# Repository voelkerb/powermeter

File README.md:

# PowerMeter

The PowerMeter is a WiFi-enabled electricity meter that can also control the connected appliance’s power status.
It enables the recording of high-frequency voltage and current waveforms or integration into smart home systems via protocols such as _MQTT_.
Additional modular components facilitate the integration of other wireless connectivity options, including LoRaWAN, and the embedding of additional sensors within the housing. 

### Clone this repo with
```bash
git clone --recurse-submodules git@github.com:voelkerb/powermeter.git
```

If you are interested in gathering the entire house energy consumption, please refer to the [SmartMeter](https://github.com/voelkerb/smartmeter) instead.

## Hardware Version _1_ vs _2_
The development commenced with hardware [version 1.0](Schematic/Version_1). It comprises an ESP8266 microcontroller and a dedicated electricity monitoring chip. As the primary objective of this project was to record voltage and current waveforms at elevated frequencies, several limitations associated with this application were addressed in hardware [version 2.0](Schematic/Version_2). This version features a more powerful microcontroller with 8MB of internal storage for data buffering, an RTC for precise sampling and timekeeping, and a full 16A relay, enabling the control of high-power appliances such as dishwashers. The USB connection present in hardware [version 1.0](Schematic/Version_1) has been eliminated, but could be reintroduced with an additional extension board.

## Why to use?
It's open source, easy to use, easy to build and offers lots of flexibility. 

The hardware is...
* tested to work reliable with 230V.
* flexible enough to be integrated into existing projects.
* extendable via a UART interface.
* rather cheap (all components sum up to around 30€).

The firmware supports...
* existing 2.4GHz WPA2 networks or can create its own network.
* to receive commands via USB, TCP or MQTT.
* to store the configuration in the internal non volatile memory.
* to provide data at sampling rates from 1/5Hz all the way up to 8kHz.
* to calibrate the measurements.
* integration into most existing smart home systems e.g. HomeKit (via homebridge and MQTT).
* FFMpeg streaming. This allows to store high frequency data directly into files (e.g. MKV).

## How to build one?
Are you interested in constructing your own PowerMeter? Since the PCBs are provided in this repository, you can simply assemble your own.

Depending on your specific requirements, you may choose to build either [Version 1.0](/Schematic/Version_1) or [Version 2.0](/Schematic/Version_2).
* [Version 1.0](/Schematic/Version_1) incorporates an ESP8266 microcontroller and a 10A solid-state relay.
    * Advantages:
        * The components are more cost-effective (approximately 30€).
        * It includes a USB interface for uploading the firmware or streaming data.
    * Disadvantages:
        * It lacks modularity.
        * The 10A relay can only switch connected appliances with a maximum power consumption of less than 2300 Watt.
* [Version 2.0](/Schematic/Version_2) features an ESP32 microcontroller and a 16A bistable relay.
    * Advantages:
        * You can switch appliances with a maximum power consumption of up to 3600 Watt.
        * It possesses a multi-core microcontroller that also supports Bluetooth.
        * 8MB of internal storage enables data buffering. If you stream high-frequency data at, for instance, 2kHz, this can accommodate up to 500s of data during network interruptions.
        * An RTC maintains timekeeping, allowing you to synchronize sampling rates during high-frequency sampling.
        * It can be extended by stacking additional modules on an extension header.
    * Disadvantages:
        * The cost of the components is slightly higher (approximately 35€).

Steps to build your own PowerMeter:

1. Create the PCB ([version 1.0](/Schematic/Version_1)) or [version 2.0](/Schematic/Version_2))). We recommend using [JLC PCB](https://jlcpcb.com) because it’s very affordable and the quality is still good.
2. Purchase the components listed in the [BOM](/BOM) (Bill of Materials).
3. Solder everything together. We used a small reflow oven, but a fine soldering iron could also be used.
4. Buy a matching housing. We highly recommend using [this one](https://www.conrad.de/de/p/bopla-eletec-se-432-de-cee-stecker-gehaeuse-120-x-65-x-50-abs-polycarbonat-lichtgrau-graphitgrau-1-st-522228.html) because the PCB was specially designed for it, the mounting holes match, and it’s safe to use with 230V. We also tried custom 3D prints (see [CAD](/CAD)), but it’s at your own risk.

5. Wire the PowerMeters using the provided diagram. 

6. Upload the [firmware](/Firmware) according to the instructions for your version. 
7. Interface with the PowerMeter according to the protocol documented [here](/docu/README_Firmware_Cmds.md) 

# Use cases
## Smart homes
There are plenty of use cases for a smart plug inside a smart home.
* Switch appliances _on_ and _off_ using a voice assistant or your smartphone
* Include it in home automation software to switch appliances based on automations, e.g.: 
    * Switch appliances _on_ and _off_ by time of day.
    * Switch appliances _off_ automatically at standby consumption.
    * Trigger an alert if the consumption exceeds a limit.

* Monitor the power consumption of an appliance over day. See this faulty fridge as an example.

## For research purpose
* Analyze high frequency voltage and current waveforms.

* Record high frequency electricity datasets (see e.g. the [FIRED](https://github.com/voelkerb/FIRED_dataset_helper) dataset which can be used for Non-Intrusive Load Monitoring).

# License:
## Firmware:
Copyright (c) 2019 Benjamin Völker. All rights reserved.
This work is licensed under the terms of the [CC 4.0 licence](https://creativecommons.org/licenses/by/4.0/).

## Hardware:
Copyright (c) 2019 Benjamin Völker. All rights reserved.
This work is licensed under the terms of the [TAPR Open Hardware License](https://web.tapr.org/TAPR_Open_Hardware_License_v1.0.txt).

# Reference

Please cite our publications if you compare to or use this system:
* Benjamin Völker, Philipp M. Scholl, and Bernd Becker. 2019. Semi-Automatic Generation and Labeling of Training Data for Non-intrusive Load Monitoring. In Proceedings of the Tenth ACM International Conference on Future Energy Systems (e-Energy '19). Association for Computing Machinery, New York, NY, USA, 17–23. DOI:https://doi.org/10.1145/3307772.3328295
 
* Benjamin Völker, Marc Pfeifer, Philipp M. Scholl, and Bernd Becker. 2020. FIRED: A Fully-labeled hIgh-fRequency Electricity Disaggregation Dataset. In Proceedings of the 7th ACM International Conference on Systems for Energy-Efficient Buildings, Cities, and Transportation (BuildSys '20). Association for Computing Machinery, New York, NY, USA, 294–297. DOI:https://doi.org/10.1145/3408308.3427623

* Völker, B.; Pfeifer, M.; Scholl, P.M.; Becker, B. A Framework to Generate and Label Datasets for Non-Intrusive Load Monitoring. Energies 2021, 14, 75. https://doi.org/10.3390/en14010075

Kudos also go to Pascal Verboket & Valentin Czisch for developing the first draft schematics prior to [Version 1.0](/Schematic/Version_1).

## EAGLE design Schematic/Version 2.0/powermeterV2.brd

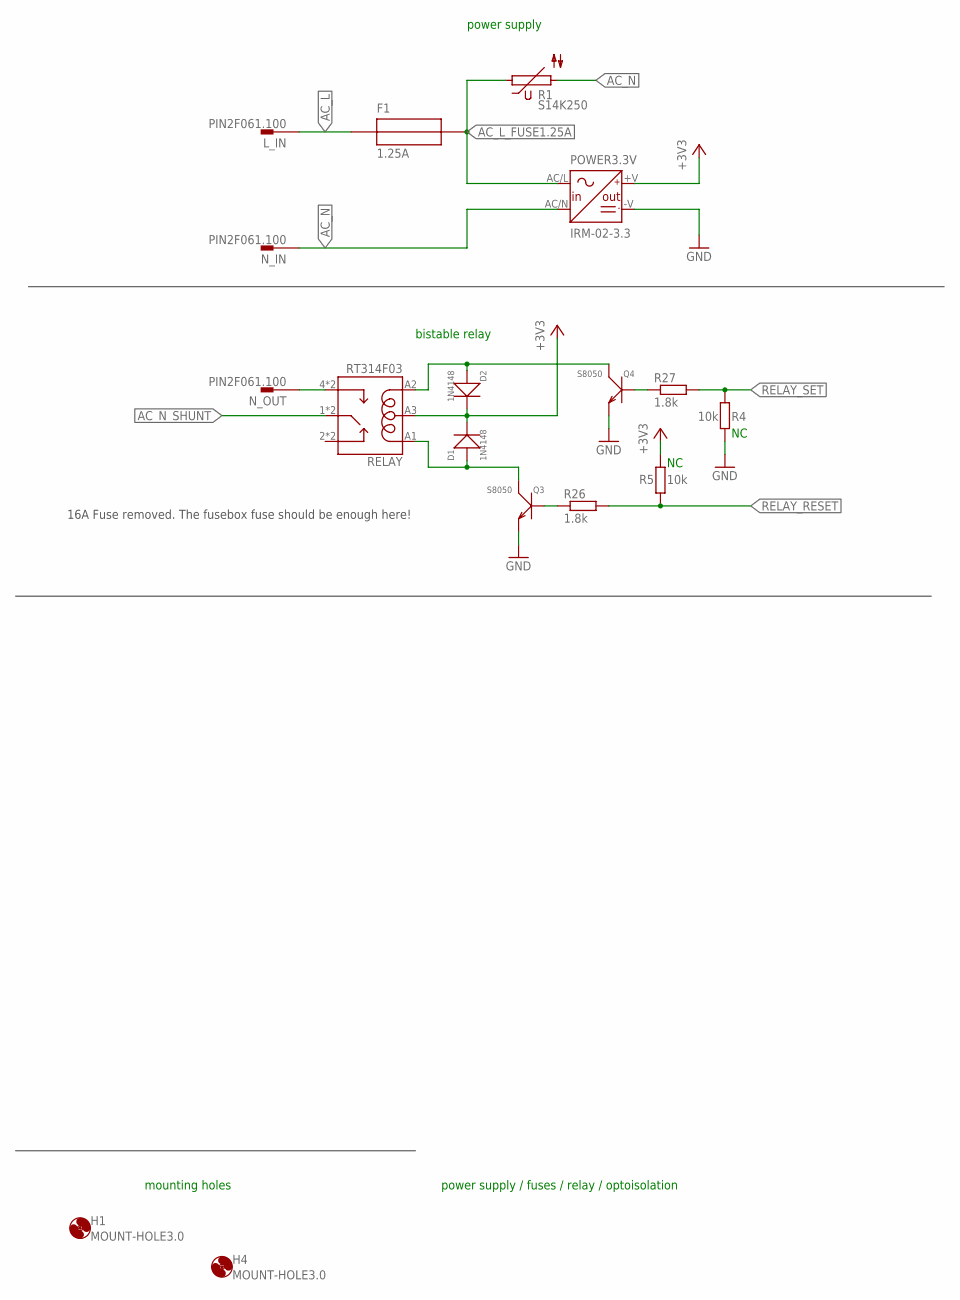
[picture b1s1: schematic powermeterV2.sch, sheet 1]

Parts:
D1, D2: 1N4148; LL-34
F1: 1.25A; SMD_FUSE
H1, H4: MOUNT-HOLE3.0; 3,0
L_IN: PIN2F061.100; F061.100
N_IN: PIN2F061.100; F061.100
N_OUT: PIN2F061.100; F061.100
POWER3.3V: IRM-02-3.3; MW_IRM-02
Q3, Q4: S8050; SOT-23
R1: S14K250
R4, R5: 10k; R0402
R26, R27: 1.8k; R0402
RELAY: RT314F03; RELAY_RT314F03

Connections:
+3V3: D1.C (-), D2.C (-), POWER3.3V.+V (+V_OUT), R5.2, RELAY.A3; also elsewhere on the board
AC_L: F1.P$1 (1), L_IN.A1, L_IN.A2; also elsewhere on the board
AC_L_FUSE1.25A: F1.P$2 (2), POWER3.3V.AC/L (L), R1.1
AC_N: N_IN.A1, N_IN.A2, POWER3.3V.AC/N (N), R1.2; also elsewhere on the board
AC_N_SHUNT: RELAY.1 (11), RELAY.11; also elsewhere on the board
GND: POWER3.3V.-V (-V_OUT), Q3.2 (E), Q4.2 (E), R4.2; also elsewhere on the board
unnamed: N_OUT.A1, N_OUT.A2, RELAY.4 (14), RELAY.14
unnamed: Q3.1 (B), R26.1
unnamed: D1.A (+), Q3.3 (C), RELAY.A1
unnamed: Q4.1 (B), R27.1
unnamed: D2.A (+), Q4.3 (C), RELAY.A2
RELAY_RESET: R5.1, R26.2; also elsewhere on the board
RELAY_SET: R4.1, R27.2; also elsewhere on the board

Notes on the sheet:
power supply / fuses / relay / optoisolation
power supply
bistable relay
mounting holes
16A Fuse removed. The fusebox fuse should be enough here!

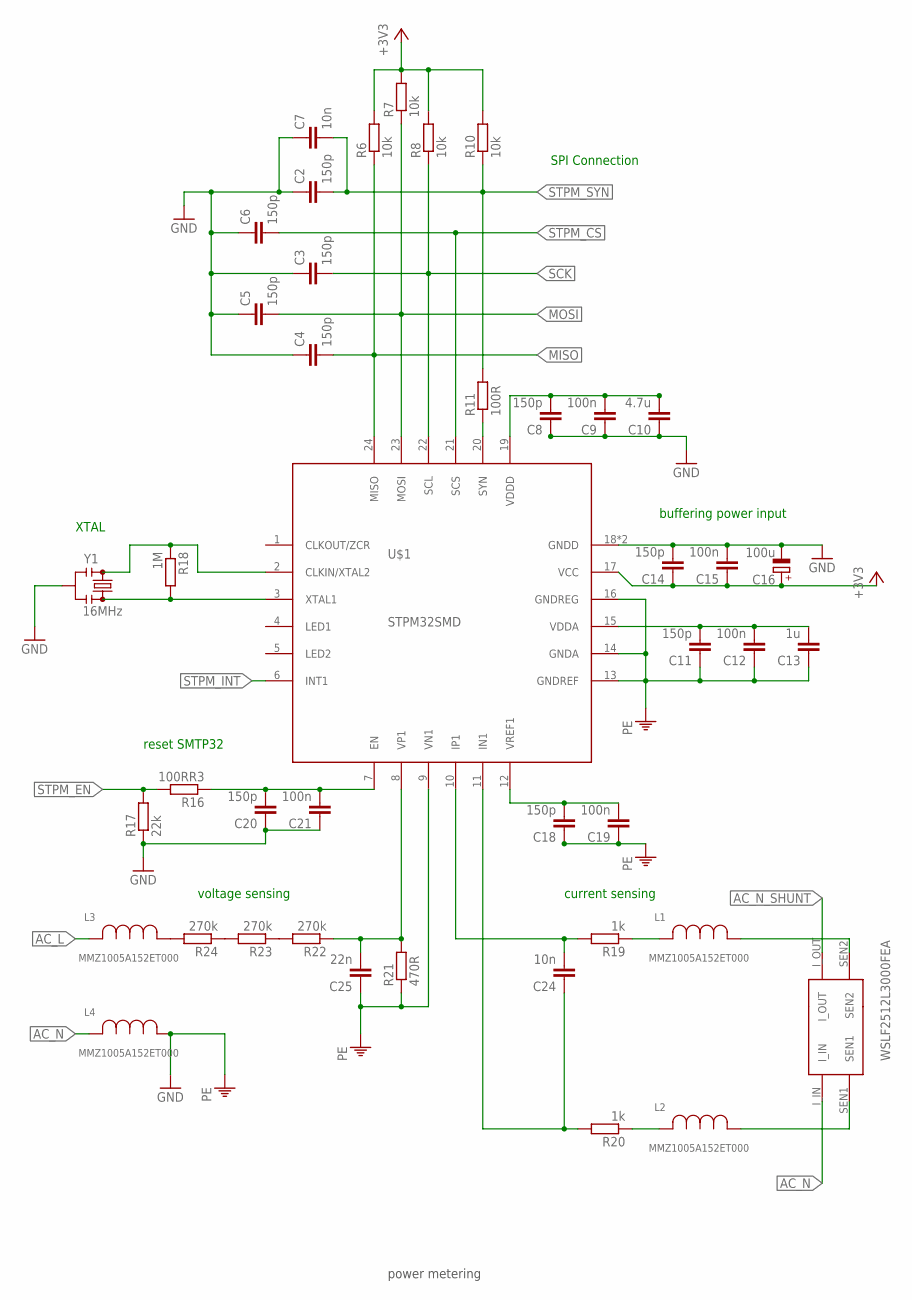
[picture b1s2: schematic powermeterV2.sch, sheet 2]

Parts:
C2, C3, C4, C5, C6, C8, C11, C14, C18, C20: 150p; C0402
C7, C24: 10n; C0603
C9, C12, C15, C19, C21: 100n; C0603
C10: 4.7u; C0805
C13: 1u; C0603
C16: 100u; D/7343-31W
C25: 22n; C0603
L1, L2, L3, L4: MMZ1005A152ET000; IND_1005
R6, R7, R8, R10: 10k; R0603
R11: 100R; R0603
R16: 100RR3; R0603
R17: 22k; R0603
R18: 1M; R0603
R19, R20: 1k; R0603
R21: 470R; M1206
R22, R23, R24: 270k; M1206
SHUNT: WSLF2512L3000FEA; SMD_SHUNT
U$1: STPM32SMD; QFN24
Y1: 16MHz; RESONATOR-SMD-3.2X1.3

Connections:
+3V3: C14.1, C15.1, C16.+, R6.2, R7.2, R8.2, R10.2, U$1.17 (VCC); also elsewhere on the board
AC_L: L3.2; also elsewhere on the board
AC_N: L4.2, SHUNT.I_IN; also elsewhere on the board
AC_N_SHUNT: SHUNT.I_OUT; also elsewhere on the board
DC_GND1: C18.2, C19.2, U$1.12 (VREF1)
DC_GND2: C20.2, C21.2, R16.1, U$1.7 (EN)
GND: C2.1, C3.1, C4.1, C5.1, C6.1, C7.1, C8.1, C9.1, C10.1, C11.1, C12.1, C13.1, C14.2, C15.2, C16.-, C18.1, C19.1, C20.1, C21.1, C25.1, L4.1, R17.1, R21.1, U$1.9 (VN1), U$1.13 (GNDREF), U$1.14 (GNDA), U$1.16 (GNDREG), U$1.18 (GNDD), U$1.EXP (GNDD), Y1.2; also elsewhere on the board
MISO: C4.2, R6.1, U$1.24 (MISO); also elsewhere on the board
MOSI: C5.2, R7.1, U$1.23 (MOSI); also elsewhere on the board
unnamed: C8.2, C9.2, C10.2, U$1.19 (VDDD)
unnamed: C11.2, C12.2, C13.2, U$1.15 (VDDA)
unnamed: R18.2, U$1.3 (XTAL1), Y1.3
unnamed: R18.1, U$1.2 (CLKIN/XTAL2), Y1.1
unnamed: C24.1, R20.2, U$1.11 (IN1)
unnamed: R11.1, U$1.20 (SYN)
unnamed: C24.2, R19.2, U$1.10 (IP1)
unnamed: C25.2, R21.2, R22.1, U$1.8 (VP1)
unnamed: R23.2, R24.1
unnamed: R22.2, R23.1
unnamed: L3.1, R24.2
unnamed: L1.2, R19.1
unnamed: L2.2, R20.1
unnamed: L1.1, SHUNT.SEN2
unnamed: L2.1, SHUNT.SEN1
SCK: C3.2, R8.1, U$1.22 (SCL); also elsewhere on the board
STPM_CS: C6.2, U$1.21 (SCS); also elsewhere on the board
STPM_EN: R16.2, R17.2; also elsewhere on the board
STPM_INT: U$1.6 (INT1)
STPM_SYN: C2.2, C7.2, R10.1, R11.2; also elsewhere on the board

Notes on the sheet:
power metering
SPI Connection
buffering power input
reset SMTP32
XTAL
current sensing
voltage sensing

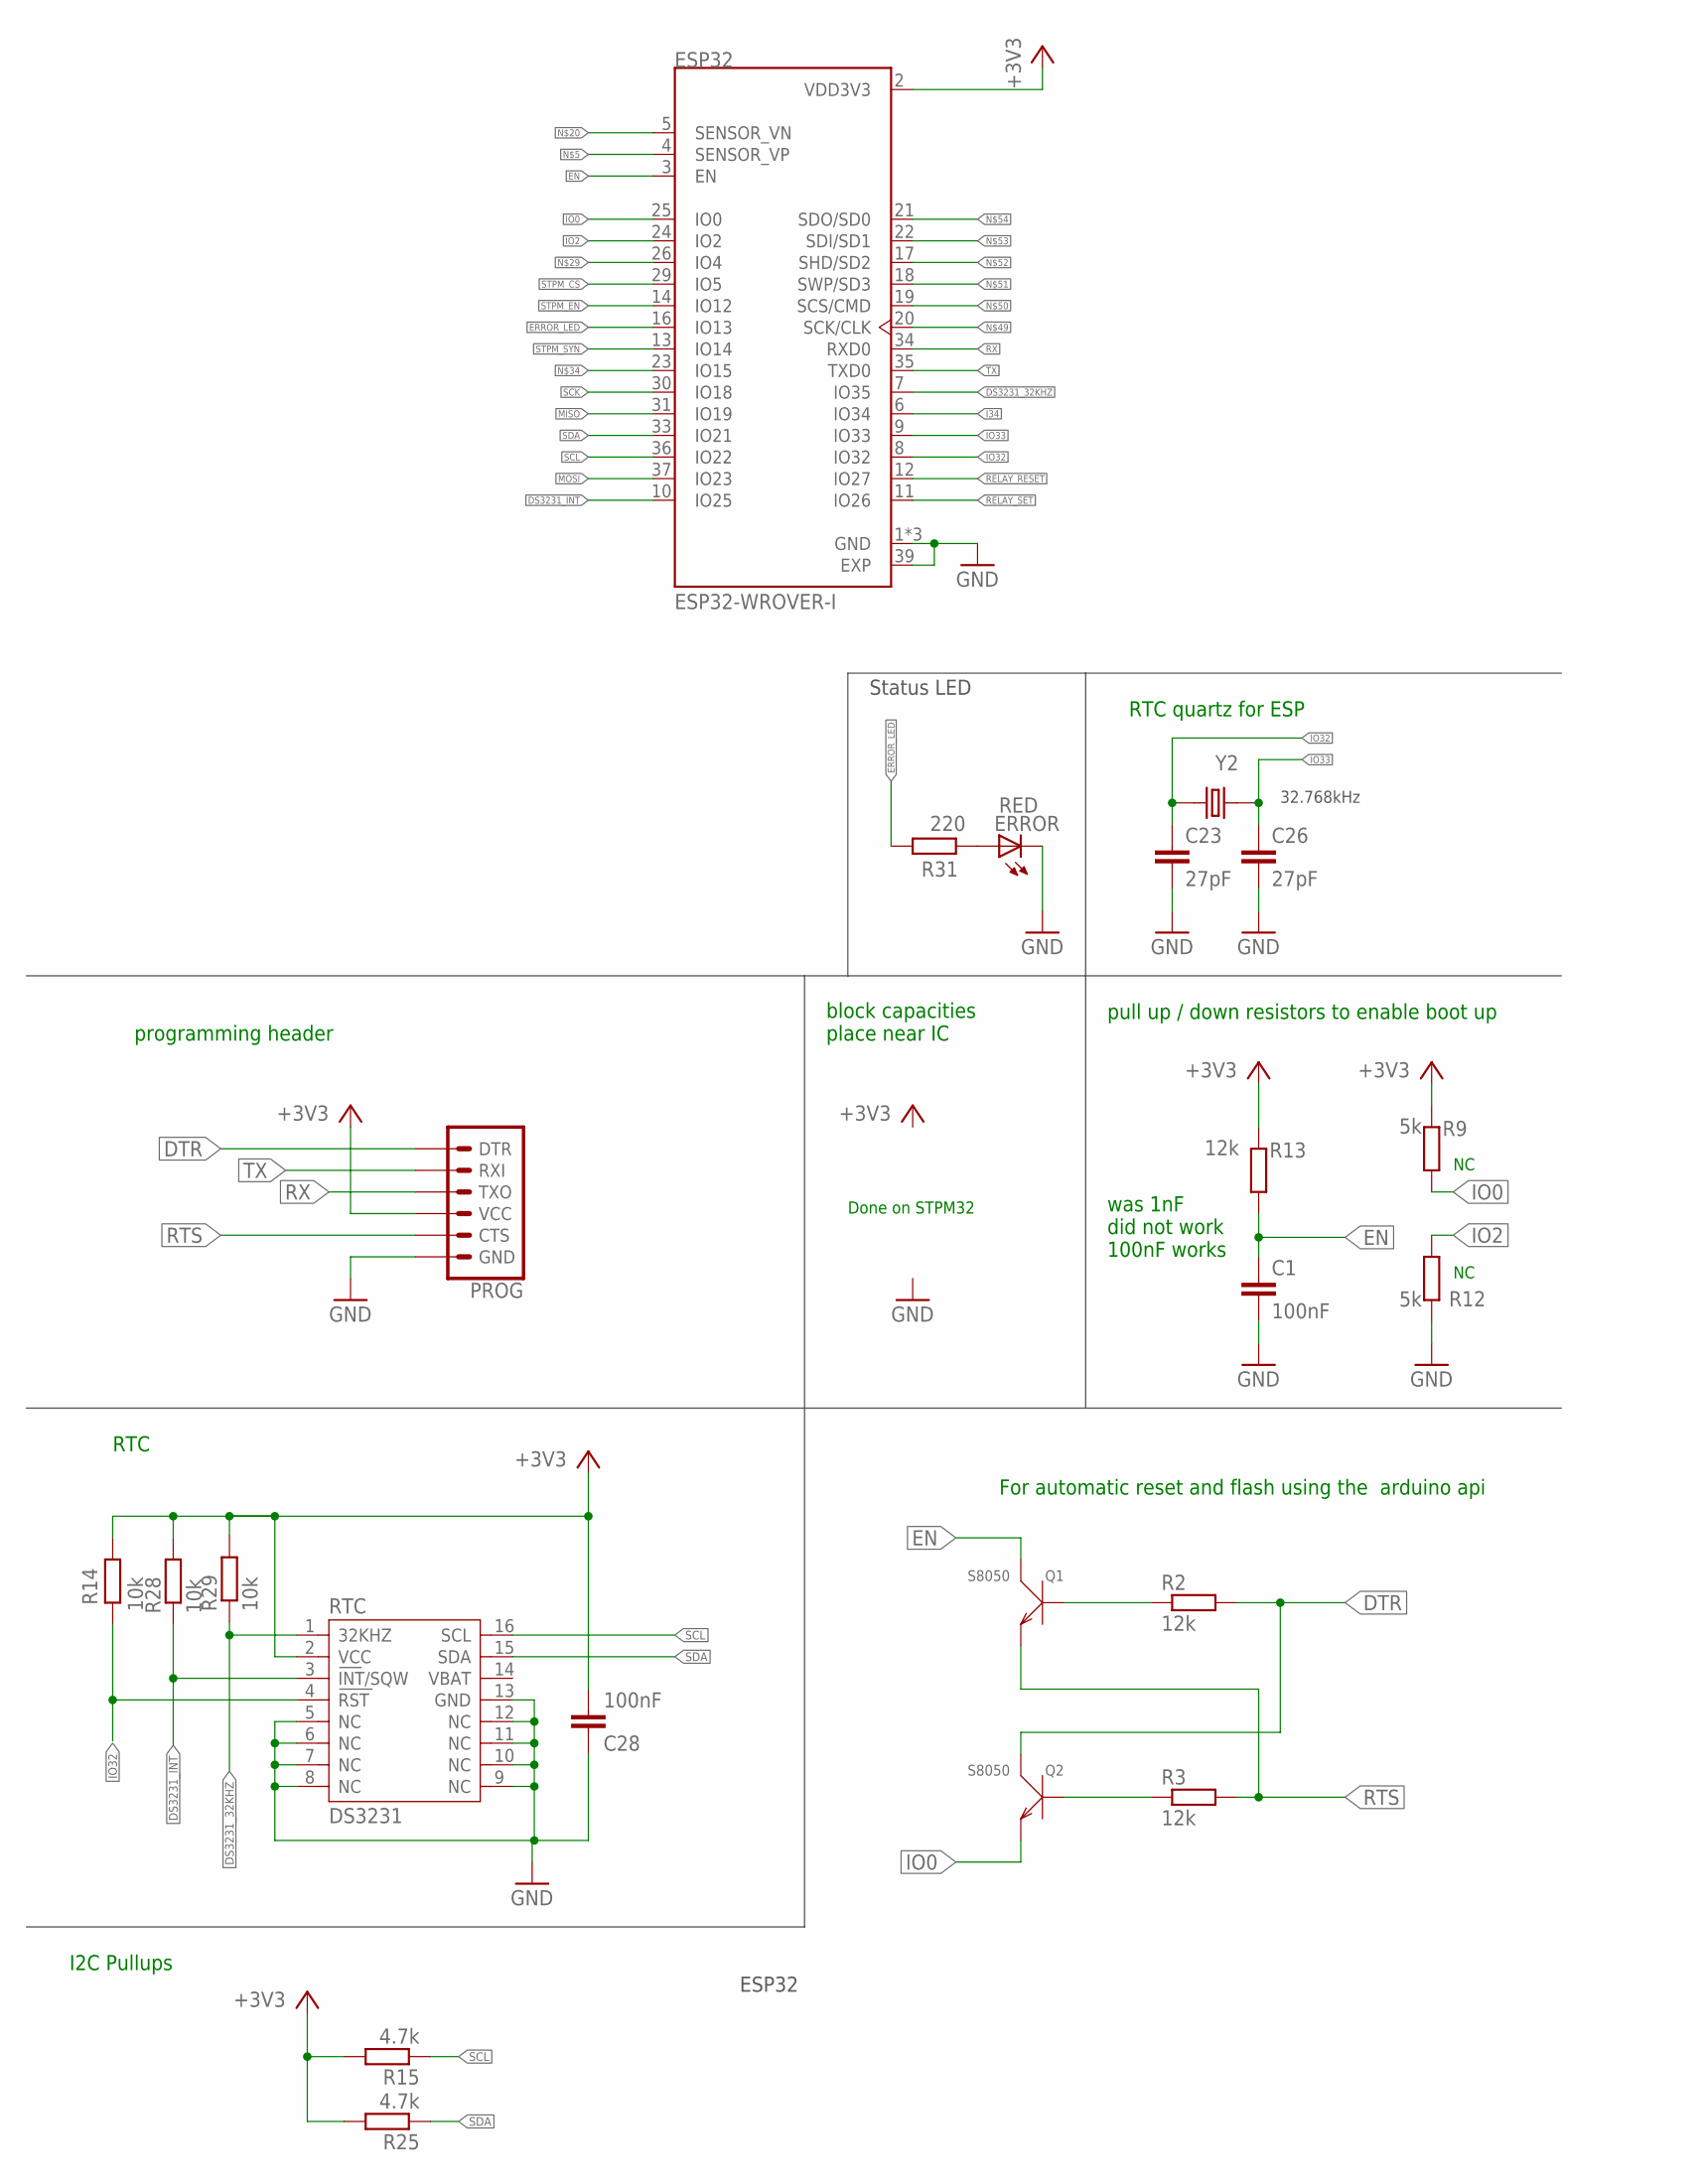
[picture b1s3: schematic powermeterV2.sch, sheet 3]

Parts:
C1, C28: 100nF; C0402
C23, C26: 27pF; C0402
ERROR: RED; CHIP-LED0805
ESP32: ESP32-WROVER-I; XCVR_ESP32-WROVER-I
PROG: 6_PIN_SERIAL_TARGET; 1X06
Q1, Q2: S8050; SOT-23
R2, R3, R13: 12k; R0402
R9, R12: 5k; R0402
R14, R28, R29: 10k; R0603
R15, R25: 4.7k; R0603
R31: 220; R0603
RTC: DS3231
Y2: NX2012SA-32.768K-STD-MUB-1; XTAL_NX2012SA-32.768K-STD-MUB-1

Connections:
+3V3: C28.2, ESP32.2 (VDD3V3), PROG.4 (VCC), R9.1, R13.1, R14.1, R15.2, R25.2, R28.2, R29.2, RTC.2 (VCC); also elsewhere on the board
DS3231_32KHZ: ESP32.7 (IO35), R29.1, RTC.1 (32KHZ)
DS3231_INT: ESP32.10 (IO25), R28.1, RTC.3 (INT/SQW)
DTR: PROG.1 (DTR), Q2.3 (C), R2.2
EN: C1.1, ESP32.3 (EN), Q1.3 (C), R13.2
ERROR_LED: ESP32.16 (IO13), R31.1
GND: C1.2, C23.2, C26.2, C28.1, ERROR.C, ESP32.1 (GND), ESP32.15 (GND), ESP32.38 (GND), ESP32.39 (EXP), PROG.6 (GND), R12.1, RTC.5 (NC), RTC.6 (NC), RTC.7 (NC), RTC.8 (NC), RTC.9 (NC), RTC.10 (NC), RTC.11 (NC), RTC.12 (NC), RTC.13 (GND); also elsewhere on the board
I34: ESP32.6 (IO34)
IO0: ESP32.25 (IO0), Q2.2 (E), R9.2
IO2: ESP32.24 (IO2), R12.2
IO32: C23.1, ESP32.8 (IO32), R14.2, RTC.4 (RST), Y2.1
IO33: C26.1, ESP32.9 (IO33), Y2.2
MISO: ESP32.31 (IO19); also elsewhere on the board
MOSI: ESP32.37 (IO23); also elsewhere on the board
unnamed: Q1.1 (B), R2.1
unnamed: Q2.1 (B), R3.1
unnamed: ERROR.A, R31.2
RELAY_RESET: ESP32.12 (IO27); also elsewhere on the board
RELAY_SET: ESP32.11 (IO26); also elsewhere on the board
RTS: PROG.5 (CTS), Q1.2 (E), R3.2
RX: ESP32.34 (RXD0), PROG.3 (TXO)
SCK: ESP32.30 (IO18); also elsewhere on the board
SCL: ESP32.36 (IO22), R15.1, RTC.16 (SCL)
SDA: ESP32.33 (IO21), R25.1, RTC.15 (SDA)
STPM_CS: ESP32.29 (IO5); also elsewhere on the board
STPM_EN: ESP32.14 (IO12); also elsewhere on the board
STPM_SYN: ESP32.13 (IO14); also elsewhere on the board
TX: ESP32.35 (TXD0), PROG.2 (RXI)

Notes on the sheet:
pull up / down resistors to enable boot up
For automatic reset and flash using the arduino api
ESP32
block capacities place near IC
Done on STPM32
32.768kHz
RTC quartz for ESP
RTC
programming header
I2C Pullups
Status LED
was 1nF did not work 100nF works

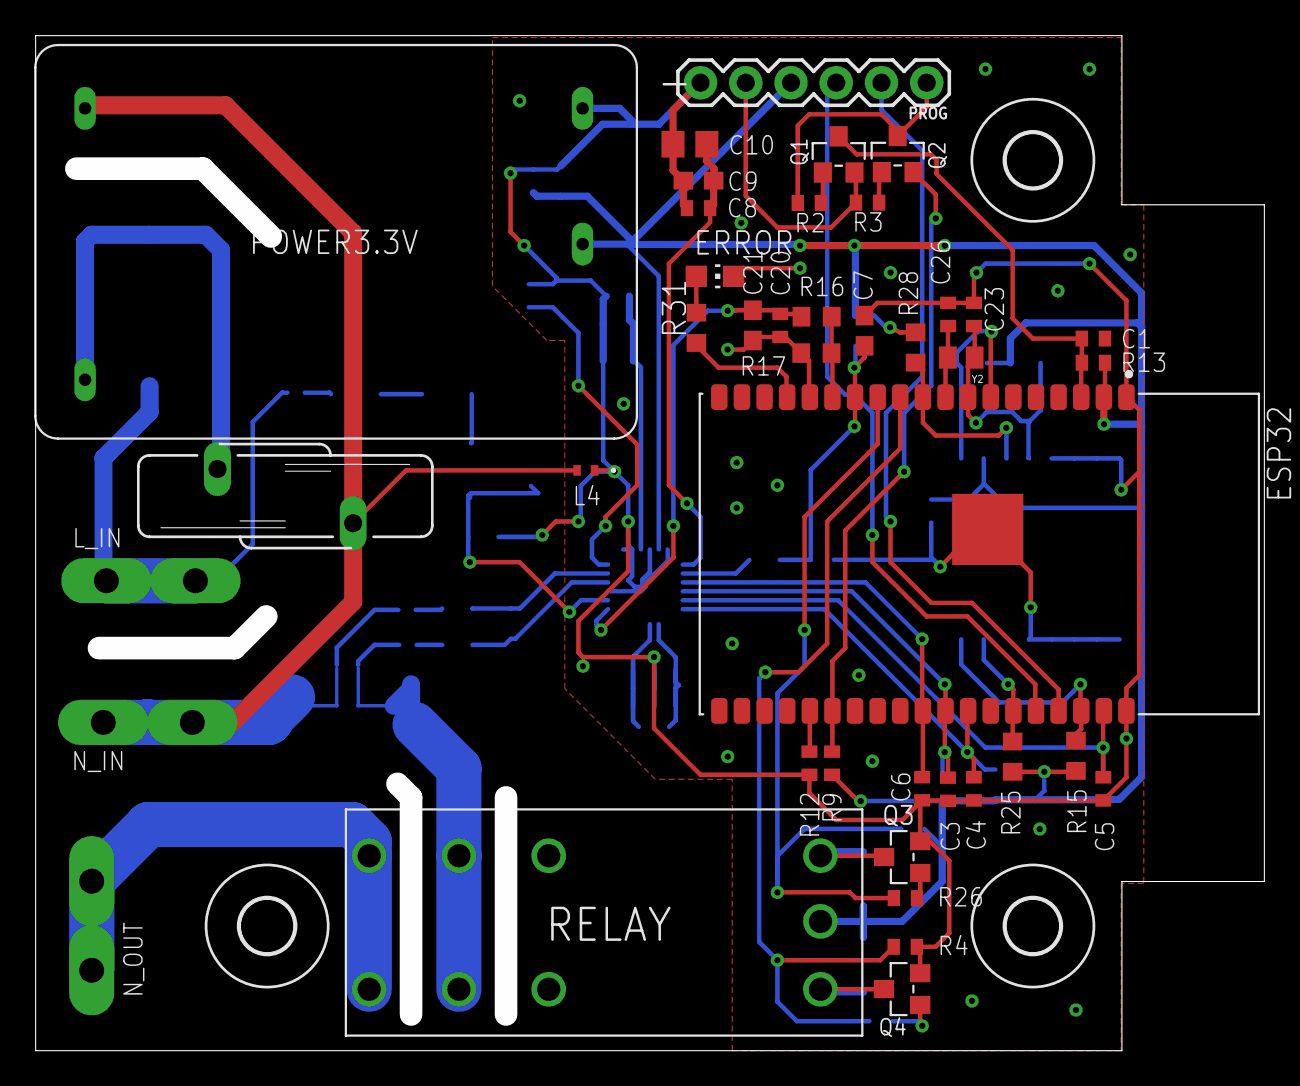
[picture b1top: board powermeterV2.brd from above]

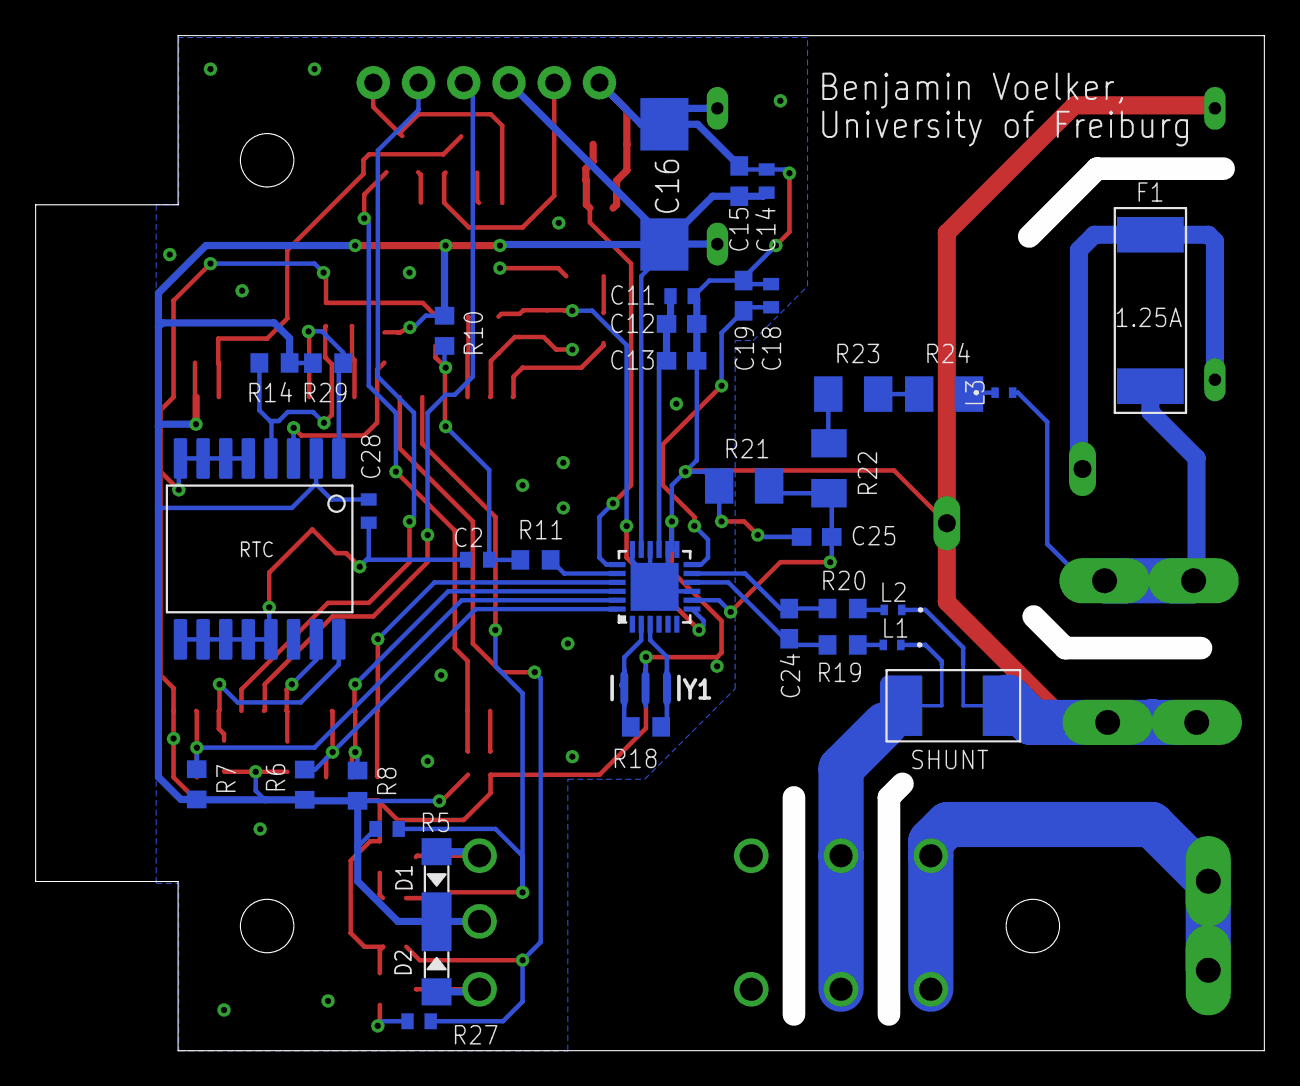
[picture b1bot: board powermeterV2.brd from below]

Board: 2 copper layers, 67.7 x 55.7 mm, 82 parts (38 on the bottom side), 53 nets.

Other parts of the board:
H2: MOUNT-HOLE3.0; 3,0

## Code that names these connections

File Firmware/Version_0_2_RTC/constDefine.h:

// Serial Speed and DEBUG option
#define SERIAL_SPEED 2000000
// #define DEBUG_DEEP
#define SENT_LIFENESS_TO_CLIENTS


#define VERSION "0.2_x_rtc"

// Default values
#define STANDARD_UDP_PORT 54323
#define STANDARD_TCP_SAMPLE_PORT 54321
#define STANDARD_TCP_STREAM_PORT 54322
#define DEFAULT_SR 4000


// Location time difference between us (Freiburg, Germany) and NTP time 
#define LOCATION_TIME_OFFSET 7200 // 2 hours or (2*60*60)


const char * LOG_FILE = "/log.txt";

const char* ntpServerName = "time.uni-freiburg.de";//"0.de.pool.ntp.org";

const char LOG_PREFIX_SERIAL[] = "";
const char LOG_PREFIX[] = "Info:";

// Pin definitions
// Red error led for first flash
const int ERROR_LED = 13;

// Pins for STPM34 SPI Connection
const int STPM_CS = 5;
const int STPM_SYN = 14;
// Reset pin of STPM
const int STPM_RES = 12;

// Pins for 230V Relay
const int RELAY_PIN_S = 26;
const int RELAY_PIN_R = 27;

// Pins for RTC conenction
const int RTC_INT = 25;
const int RTC_32k = 35;
const int RTC_RST = 32;


// Buffering stuff
#define MAX_SEND_SIZE 512 // 1024
// PSRAM Buffer
const int PS_BUF_SIZE = 3*1024*1024 + 512*1024;
#define COMMAND_MAX_SIZE 400

// Communication commands
#define CMD_SAMPLE "sample"
#define CMD_SWITCH "switch"
#define CMD_STOP "stop"
#define CMD_RESTART "restart"
#define CMD_RESET "factoryReset"
#define CMD_INFO "info"
#define CMD_MDNS "mdns"
#define CMD_NTP "ntp"
#define CMD_ADD_WIFI "addWifi"
#define CMD_REMOVE_WIFI "delWifi"
#define CMD_CLEAR_LOG "clearLog"
#define CMD_GET_LOG "getLog"

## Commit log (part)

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2018-11-07 Initial commit of latest files
2018-11-07 added library for stpm32
2018-11-07 deleted
2018-11-12 Fixed regular streaming
2018-11-23 added current version
2018-12-06 Fixed that NTP timed recordings can also be startet using tcp clients
2018-12-19 Disabled Autolatching in favour of manual latching to prevent data glitches! Added CRC disable option and autolatch On option. Tested until 8kHz even if the stpm only supports 7.8125kHz.
2018-12-19 Master Merge
2018-12-20 MDNS name is now read from EEPROM, EEPROM has to be written to at least once s.t. this works
2019-01-07 added ability to set mdns name using serial or tcp command -> Command: 'n12' sets mdns name to powermeter12
2019-03-06 Changed nbuffering to a ringbuffer, version 0.1 kept. Exceptions might still occur. Mutual exclusion problem?
2019-08-05 added version 0_2_x TODO: We need SPIFFS integration to prevent data loss
2019-09-06 Ported to ESP32
2019-09-18 Firmware is now object oriented with RTC support
2019-09-27 new firmware with RTC support, PSRAM, new schematic/board with error LED, I2C pullups etc, diodes
2019-10-16 objectify + added logger, timehandler
2019-11-06 added release ota folder
2019-11-08 added new version where SPI is not in interrupt
2019-11-11 added ethernet support
2019-11-11 added submodules
2019-11-11 removed untracked submodules
2019-11-12 Removed submodule temporarly
2019-11-12 cleaned submodules
2019-11-25 added Version 1 as last version for old HW revision 1.0
2019-12-13 cleanup
2019-12-13 renamed
2019-12-13 cleanup after renaming
2020-01-20 Version renumbering. Hardware Version 1 will now work with Software Version and Hardware Version 2 requires Software Version >= 2
2020-01-21 added multiclient support for tcp
2020-01-22 minor bugfixes
2020-01-22 fixed board/schematic inconsistencies. added 100nF on IO0
2020-02-04 fixed versioning
2020-02-05 added MQTT
2020-02-06 added parsing ino file, added mqtt state request
2020-02-18 rewrite to mqtt class closing ticket 445
2020-02-18 added sampleCB function, network switch is now not possible while sampling or OTA
2020-02-19 added mqtt sampling, closing ticket #442
2020-02-19 added streamserver functionality closing feature #438
2020-02-19 hotfix of OTA not working due to streamserver connect
2020-02-20 fixed issue #453 -> null on mqtt sampling and #454 -> stop command
2020-03-09 added time server command
2020-03-09 minor bugfix
2020-03-12 Closing #459 parallel ntp sync
2020-03-13 added alldevicesettingsgetter blank file
2020-03-13 added network submodule
2020-03-13 Removed submodule
2020-03-17 Added MQTT for homebridge to close #46
2020-03-19 fixed #462 and #463
2020-04-23 added flow control, fixing #469, #470, #471, #474, used snprintf
2020-04-28 saving work for #481 #477
2020-05-13 last stable version
2020-05-18 more priority for sampling task, hopefully fixing #487
2020-05-18 minor improvements
2020-05-18 added ntp correction only for certain confidence level
2021-02-24 Speed up MQTT Reconnect and support mqtt retained switches
2021-02-24 updates submodules
2021-03-01 save
2021-03-01 resstructure
2021-03-01 submodules
2021-03-01 stash
2021-03-01 submoduels reinitialized
2021-03-01 fixed network branch
2021-03-02 added docu
2021-03-02 more docu
2021-03-02 removed zips
2021-03-02 renamed schematic folder
2021-03-02 added why to use
2021-03-02 unify version 2 and version 1 command code
2021-03-03 changed software timers to use unsigned int
2021-03-03 chenged timer to unsigned int
2021-03-03 added update poll function for networjk
2021-03-03 changed Buff size
2021-03-03 gitmodules
2021-03-18 Fixed MQTT msg too often
2021-08-03 added lorawan class
2021-08-03 added support for LoRaWAN
2021-08-03 added support for private key file
2021-08-03 no use lora class to construct message from bytes
2021-08-03 config does now use standard WIFI PWDs from external file
2021-08-03 constDefined includes private file with keys
2021-08-03 Lora support added
2021-08-03 added
2021-08-03 added preprocessor settings docu
2021-08-03 added Lorawan commands
2021-08-03 fixed lorawan port
2021-08-06 fixed submodules
2021-08-06 added functions for seconds minutes hours, etc
2021-08-06 added energy functionality
2021-08-06 packed struct
2021-08-06 fixed prot
2021-08-06 submodule behavior for version 2 is now merge
2021-08-06 define for energy data report on lifeness, energy update intv
2021-08-06 energy now double, struct packed
2021-08-06 added reset energy command
2021-08-06 added energy reset
2021-08-06 added energy accumulation
2021-08-06 added reset energy command, energy over mqtt
2021-08-06 added energy to docu, table to commands
2021-08-12 added support for energy, reset, calibration
2021-08-12 added config for energy, reset, calibration
2021-08-12 checkedout latest master
2021-08-12 deleted old eeprom addresses
2021-08-12 changed SSID length define
2021-08-12 different software timer for mqtt
2021-08-12 firmware now includes energy
2021-08-18 added sensorboard submodule with simlinks
2021-08-18 added support for sensorboard
2021-08-19 some LED patterns included
2021-08-26 new parsing and static pattern treatment
2021-08-26 each LED now indicating successfull init of a certain module
2021-08-26 fic for c++17
2021-09-17 sensor board config included
2021-09-17 const members converted to defines, SensorBoardCmds added
2021-09-17 sensorboard commands handled
2021-09-17 sensor MQTT now on separate topics
2021-09-17 added docu for sensor board commands
2021-09-20 fixed RMS voltage
2021-09-20 added energy cmds, consts are now defines
2021-09-20 Docu for energy commands
2021-09-20 new CAD
2021-09-21 fixed storeage of energy start period
2021-09-21 added pic of powermeter
2021-09-21 shrink pics
2021-10-13 submodule update
2021-10-25 rework for esp idf 2.0
2021-10-27 removed some compiler warnings
2021-10-27 latest sensorboard chechout
2022-02-09 energy over mqtt now send as Wh not kWh for better resolution
2022-03-16 added mqtt user pwd setting, mqtt intv
2022-03-20 added user pwd mqtt docu + publish interval
2022-10-29 downgraded submodules to https + sensorboard fix
2022-10-29 submodule updates
2022-10-29 update submodules
2025-11-19 Update README_Firmware_Cmds.md
    fix typo in command syntax

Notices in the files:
parts and their libraries:
SparkFun-Clocks: Licensing: Creative Commons ShareAlike 4.0 International - https://creativecommons.org/licenses/by-sa/4.0
